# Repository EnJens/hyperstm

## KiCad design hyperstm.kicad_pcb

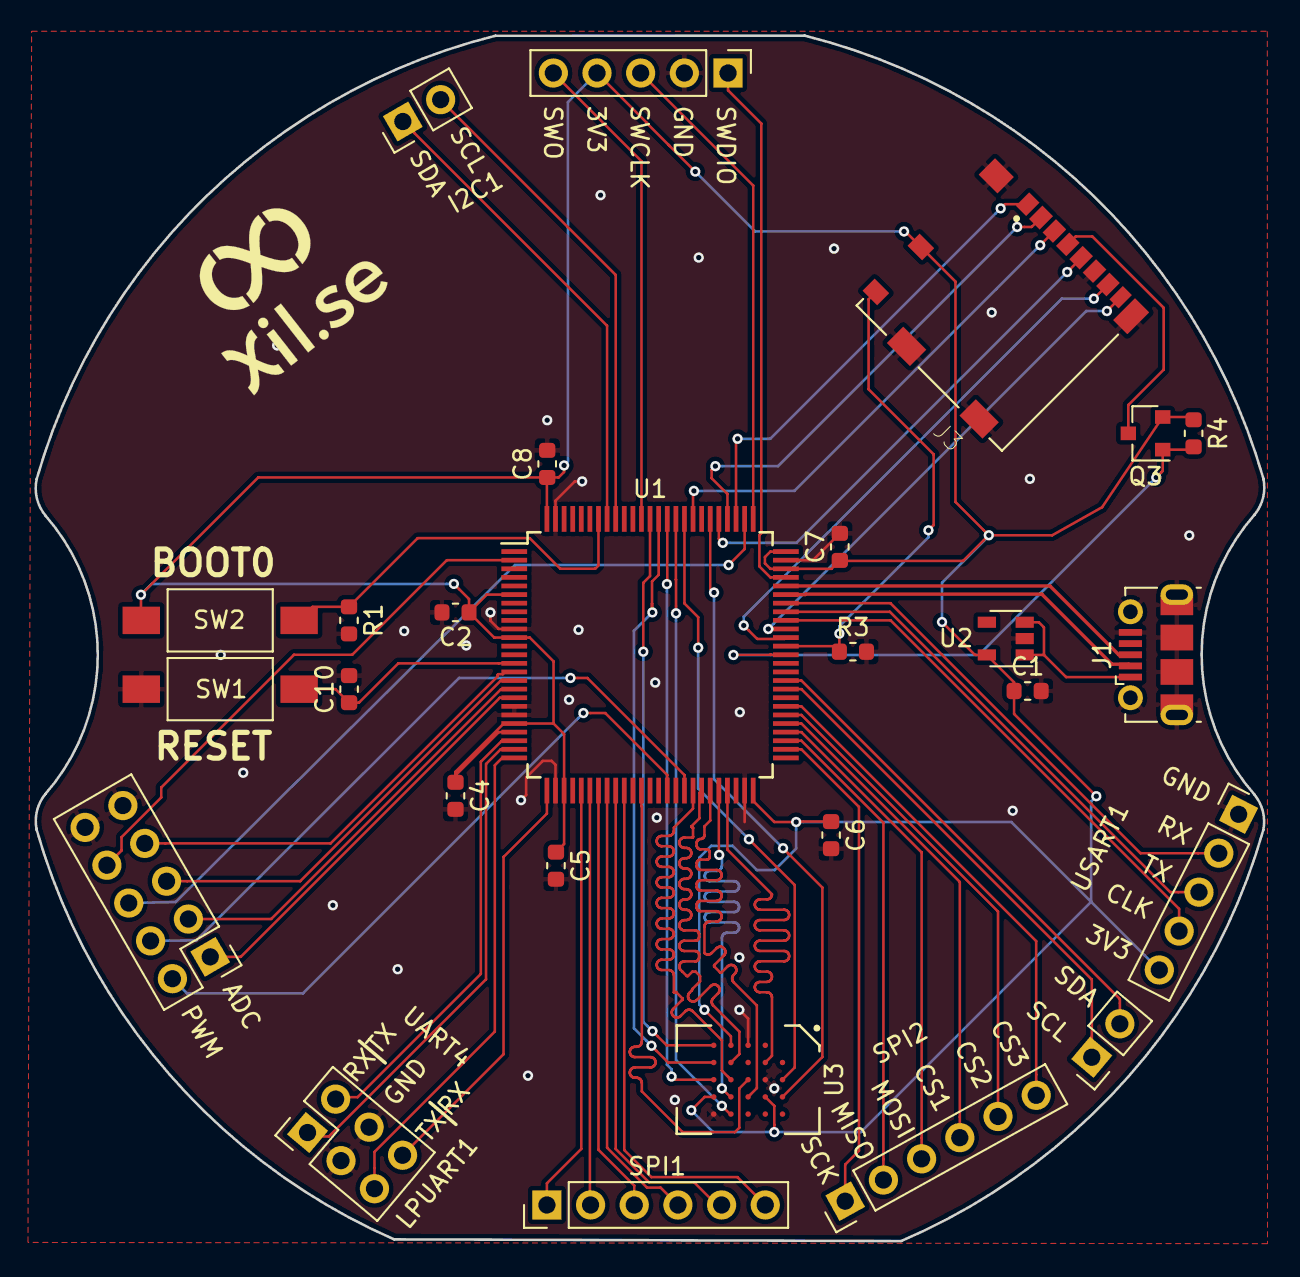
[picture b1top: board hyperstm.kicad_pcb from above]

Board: 2 copper layers, 71.5 x 70.1 mm, 27 parts (0 on the bottom side), 62 nets.

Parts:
C1: 10uF; C_0603_1608Metric
C2, C4, C5, C6, C7, C8, C10: 100nF; C_0603_1608Metric
J1: USB_B_Micro; USB_Micro-B_Molex-105017-0001
J2: DBG_HEADER; PinHeader_1x05_P2.54mm_Vertical
J3: Micro_SD_Card_Det; MOLEX_104031-0811
J4: Analog_Header; PinHeader_2x05_P2.54mm_Vertical
J5: UART_COMBO; PinHeader_2x03_P2.54mm_Vertical
J6: USART1; PinHeader_1x05_P2.54mm_Vertical
J7: SPI2; PinHeader_1x06_P2.54mm_Vertical
J8: I2C1; PinHeader_1x02_P2.54mm_Vertical
J9: I2C4; PinHeader_1x02_P2.54mm_Vertical
J10: SPI1; PinHeader_1x06_P2.54mm_Vertical
Q3: FDN340P; SOT-23
R1, R3: 10k; R_0603_1608Metric
R4: 1k; R_0603_1608Metric
SW1, SW2: SW_SPST; SW_SPST_FSMSM
U1: STM32L4R5VITx; LQFP-100_14x14mm_P0.5mm
U2: MIC5219-3.3; SOT-23-5
U3: S27KL0641; BGA-25_5x5_6.0x8.0mm

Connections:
+3V3: C1.1, C2.1, C4.1, C5.1, C6.1, C7.1, C8.1, J2.4, J3.9, J6.5, Q3.2, R4.1, SW2.1, U1.6, U1.11, U1.21, U1.22, U1.28, U1.50, U1.73, U1.75, U1.100, U2.5, U3.B4, U3.D1, U3.E4
/Microcontroller/ADC1_IN: J4.7, U1.15
/Microcontroller/ADC1_IN2: J4.5, U1.16
/Microcontroller/ADC1_IN3: J4.3, U1.17
/Microcontroller/ADC1_IN4: J4.1, U1.18
/Microcontroller/BOOT0: R1.1, SW2.2, U1.94
/Microcontroller/I2C1_SCL: J8.2, U1.92
/Microcontroller/I2C1_SDA: J8.1, U1.93
/Microcontroller/I2C4_SCL: J9.1, U1.59
/Microcontroller/I2C4_SDA: J9.2, U1.60
/Microcontroller/LPUART1_RX: J5.6, U1.26
/Microcontroller/LPUART1_TX: J5.5, U1.25
/Microcontroller/SDMMC1_DET: J3.10, R3.1, U1.64
/Microcontroller/SPI1_CS1: J10.4, U1.33
/Microcontroller/SPI1_CS2: J10.5, U1.34
/Microcontroller/SPI1_CS3: J10.6, U1.35
/Microcontroller/SPI1_MISO: J10.2, U1.31
/Microcontroller/SPI1_MOSI: J10.3, U1.32
/Microcontroller/SPI1_SCK: J10.1, U1.30
/Microcontroller/SPI2_CS1: J7.4, U1.55
/Microcontroller/SPI2_CS2: J7.5, U1.56
/Microcontroller/SPI2_CS3: J7.6, U1.57
/Microcontroller/SPI2_MISO: J7.2, U1.53
/Microcontroller/SPI2_MOSI: J7.3, U1.54
/Microcontroller/SPI2_SCK: J7.1, U1.52
/Microcontroller/SWCLK: J2.3, U1.76
/Microcontroller/SWDIO: J2.1, U1.72
/Microcontroller/SWO: J2.5, U1.89
/Microcontroller/TIM1_CH1: J4.2, U1.40
/Microcontroller/TIM1_CH2: J4.4, U1.42
/Microcontroller/TIM2_CH1: J4.6, U1.77
/Microcontroller/TIM3_CH1: J4.8, U1.2
/Microcontroller/UART4_RX: J5.1, U1.24
/Microcontroller/UART4_TX: J5.2, U1.23
/Microcontroller/USART1_CK: J6.4, U1.67
/Microcontroller/USART1_RX: J6.2, U1.69
/Microcontroller/USART_TX: J6.3, U1.68
/Microcontroller/USB_D+: J1.3, U1.71
/Microcontroller/USB_D-: J1.2, U1.70
/Microcontroller/VBUS: J1.1, U2.1, U2.3
/OCTOSPI_CLK: U1.47, U3.B2
/OCTOSPI_DQS: U1.37, U3.C3
/OCTOSPI_IO0: U1.43, U3.D3
/OCTOSPI_IO1: U1.44, U3.D2
/OCTOSPI_IO2: U1.45, U3.C4
/OCTOSPI_IO3: U1.46, U3.D4
/OCTOSPI_IO4: U1.85, U3.D5
/OCTOSPI_IO5: U1.86, U3.E3
/OCTOSPI_IO6: U1.87, U3.E2
/OCTOSPI_IO7: U1.88, U3.E1
/SDMMC1_CLK: J3.5, U1.80
/SDMMC1_CMD: J3.3, U1.83
/SDMMC1_D0: J3.7, U1.65
/SDMMC1_D1: J3.8, U1.66
/SDMMC1_D2: J3.1, U1.78
/SDMMC1_D3: J3.2, U1.79
/SDMMC1_PWR: Q3.1, R4.2, U1.63
/SDMMC1_VDD: J3.4, Q3.3
/~OCTOSPI_CS~: U1.84, U3.A3
/~OCTOSPI_RESET~: U1.81, U3.A4
GND: C1.2, C2.2, C4.2, C5.2, C6.2, C7.2, C8.2, C10.2, J1.5, J1.6, J2.2, J3.6, J3.11, J4.9, J4.10, J5.3, J5.4, J6.1, R1.2, R3.2, SW1.1, U1.10, U1.19, U1.20, U1.27, U1.49, U1.74, U1.99, U2.2, U3.B3, U3.C1, U3.E5
unnamed: C10.1, SW1.2, U1.14

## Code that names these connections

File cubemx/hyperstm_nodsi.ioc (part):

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Mcu.Name=STM32L4R5V(G-I)Tx
Mcu.Package=LQFP100
Mcu.UserName=STM32L4R5VITx
PA0.Mode=Asynchronous
PA0.Signal=UART4_TX
PA1.Mode=Asynchronous
PA1.Signal=UART4_RX
PA10.Mode=Asynchronous
PA10.Signal=USART1_RX
PA11.Mode=Device_Only
PA11.Signal=USB_OTG_FS_DM
PA12.Mode=Device_Only
PA12.Signal=USB_OTG_FS_DP
PA13\ (JTMS/SWDIO).Mode=Serial_Wire
PA13\ (JTMS/SWDIO).Signal=SYS_JTMS-SWDIO
PA14\ (JTCK/SWCLK).Mode=Serial_Wire
PA14\ (JTCK/SWCLK).Signal=SYS_JTCK-SWCLK
PA15\ (JTDI).Signal=S_TIM2_CH1
PA2.Mode=Asynchronous
PA2.Signal=LPUART1_TX
PA3.Mode=Asynchronous
PA3.Signal=LPUART1_RX
PA5.Mode=Full_Duplex_Master
PA5.Signal=SPI1_SCK
PA6.Mode=Full_Duplex_Master
PA6.Signal=SPI1_MISO
PA7.Mode=Full_Duplex_Master
PA7.Signal=SPI1_MOSI
PA8.Signal=USART1_CK
PA9.Mode=Asynchronous
PA9.Signal=USART1_TX
PB0.GPIOParameters=GPIO_Label
PB0.GPIO_Label=SPI1_CS3
PB0.Signal=GPIO_Output
PB10.Mode=OCTOSPI1_Port1_CLK
PB10.Signal=OCTOSPIM_P1_CLK
PB13.Mode=Full_Duplex_Master
PB13.Signal=SPI2_SCK
PB14.Mode=Full_Duplex_Master
PB14.Signal=SPI2_MISO
PB15.Mode=Full_Duplex_Master
PB15.Signal=SPI2_MOSI
PB2.Mode=OCTOSPI1_Port1_DQS
PB2.Signal=OCTOSPIM_P1_DQS
PB6.Mode=I2C
PB6.Signal=I2C1_SCL
PB7.Mode=I2C
PB7.Signal=I2C1_SDA
PC0.Signal=ADCx_IN1
PC1.Signal=ADCx_IN2
PC10.Mode=SD_4_bits_Wide_bus
PC10.Signal=SDMMC1_D2
PC11.Mode=SD_4_bits_Wide_bus
PC11.Signal=SDMMC1_D3
PC12.Mode=SD_4_bits_Wide_bus
PC12.Signal=SDMMC1_CK
PC2.Signal=ADCx_IN3
PC3.Signal=ADCx_IN4
PC4.GPIOParameters=GPIO_Label
PC4.GPIO_Label=SPI1_CS1
PC4.Signal=GPIO_Output
PC5.GPIOParameters=GPIO_Label
PC5.GPIO_Label=SPI1_CS2
PC5.Signal=GPIO_Output
PC6.GPIOParameters=GPIO_Label
PC6.GPIO_Label=SDMMC1_PWR
PC6.Signal=GPIO_Output
PC7.GPIOParameters=GPIO_Label
PC7.GPIO_Label=SDMMC1_DET
PC7.Signal=GPIO_Input
PC8.Mode=SD_4_bits_Wide_bus
PC8.Signal=SDMMC1_D0
PC9.Mode=SD_4_bits_Wide_bus
PC9.Signal=SDMMC1_D1
PD0.GPIOParameters=GPIO_Label
PD0.GPIO_Label=OCTOSPIM_P1_NRESET
PD0.Signal=GPIO_Output
PD10.GPIOParameters=GPIO_Label
PD10.GPIO_Label=SPI2_CS3
PD10.Signal=GPIO_Output
PD12.Mode=I2C
PD12.Signal=I2C4_SCL
PD13.Mode=I2C
PD13.Signal=I2C4_SDA
PD2.Mode=SD_4_bits_Wide_bus
PD2.Signal=SDMMC1_CMD
PD3.Mode=OCTOSPI1_Port2_NCS
PD3.Signal=OCTOSPIM_P2_NCS
PD4.Mode=OCTOSPI1_IOH1_Port1H
PD4.Signal=OCTOSPIM_P1_IO4
PD5.Mode=OCTOSPI1_IOH1_Port1H
PD5.Signal=OCTOSPIM_P1_IO5
PD6.Mode=OCTOSPI1_IOH1_Port1H
PD6.Signal=OCTOSPIM_P1_IO6
PD7.Mode=OCTOSPI1_IOH1_Port1H
PD7.Signal=OCTOSPIM_P1_IO7
PD8.GPIOParameters=GPIO_Label
PD8.GPIO_Label=SPI2_CS1
PD8.Signal=GPIO_Output
PD9.GPIOParameters=GPIO_Label
PD9.GPIO_Label=SPI2_CS2
PD9.Signal=GPIO_Output
PE11.Signal=S_TIM1_CH2
PE12.Mode=OCTOSPI1_IOL_Port1L2
PE12.Signal=OCTOSPIM_P1_IO0
PE13.Mode=OCTOSPI1_IOL_Port1L2
PE13.Signal=OCTOSPIM_P1_IO1
PE14.Mode=OCTOSPI1_IOL_Port1L2
PE14.Signal=OCTOSPIM_P1_IO2
PE15.Mode=OCTOSPI1_IOL_Port1L2
PE15.Signal=OCTOSPIM_P1_IO3
PE3.Signal=S_TIM3_CH1
PE9.Signal=S_TIM1_CH1
RCC.HSE_VALUE=8000000
board=custom

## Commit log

2018-06-21 Initial schematic setup
2018-06-21 Add cubemx setup
2018-07-19 More work
2018-07-22 More updates
2018-07-25 More routing
2018-07-26 FInal touches
2018-09-24 Rev 1
2020-04-18 Fix outline
